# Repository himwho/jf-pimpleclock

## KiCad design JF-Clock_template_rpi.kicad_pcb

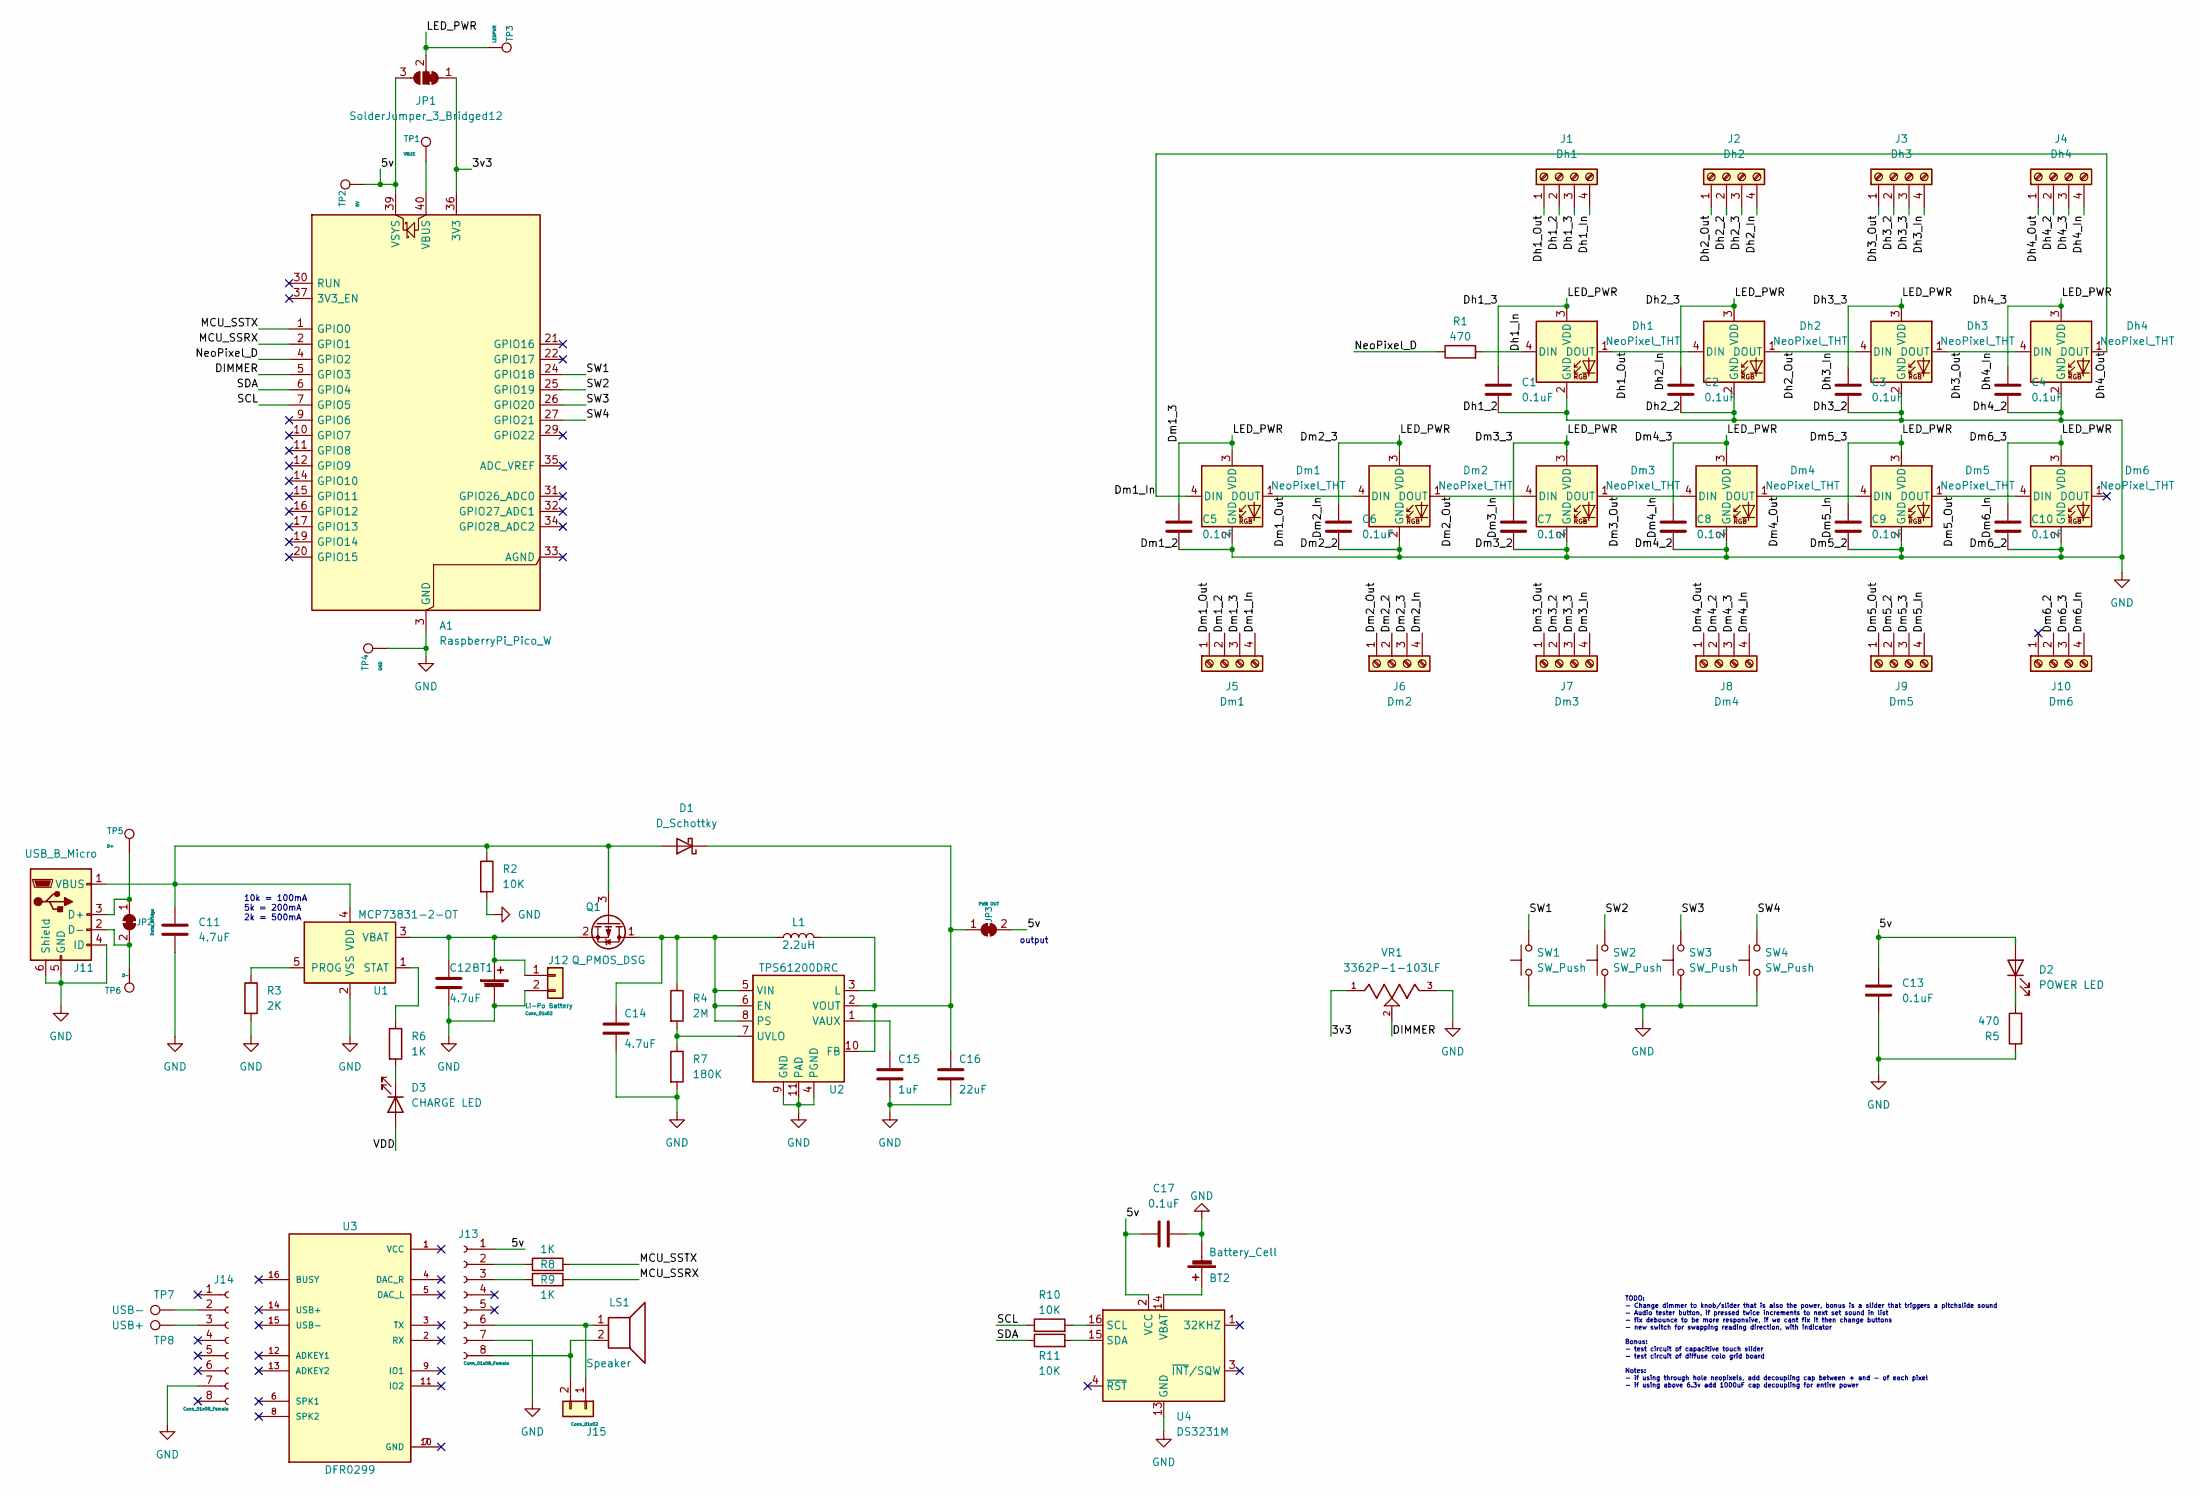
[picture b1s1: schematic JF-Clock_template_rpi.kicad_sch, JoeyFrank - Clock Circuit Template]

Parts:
A1: RaspberryPi_Pico_W; RaspberryPi_Pico_Common_THT
BT1: Li-Po Battery
BT2: Battery_Cell; BatteryHolder_Keystone_1060_1x2032
C1, C2, C3, C4, C5, C6, C7, C8, C9, C10, C13, C17: 0.1uF; C_0805_2012Metric
C11, C12, C14: 4.7uF; C_0805_2012Metric
C15: 1uF; C_0805_2012Metric
C16: 22uF; C_0805_2012Metric
D1: D_Schottky; D_SMA
D2: POWER LED; LED_0603_1608Metric
D3: CHARGE LED; LED_0603_1608Metric
Dh1, Dh2, Dh3, Dh4: NeoPixel_THT; LED_D5.0mm-4_RGB
Dm1, Dm2, Dm3, Dm4, Dm5, Dm6: NeoPixel_THT; LED_D5.0mm-4_RGB
J1: Dh1; TerminalBlock_4Ucon_1x04_P3.50mm_Vertical
J2: Dh2; TerminalBlock_4Ucon_1x04_P3.50mm_Vertical
J3: Dh3; TerminalBlock_4Ucon_1x04_P3.50mm_Vertical
J4: Dh4; TerminalBlock_4Ucon_1x04_P3.50mm_Vertical
J5: Dm1; TerminalBlock_4Ucon_1x04_P3.50mm_Vertical
J6: Dm2; TerminalBlock_4Ucon_1x04_P3.50mm_Vertical
J7: Dm3; TerminalBlock_4Ucon_1x04_P3.50mm_Vertical
J8: Dm4; TerminalBlock_4Ucon_1x04_P3.50mm_Vertical
J9: Dm5; TerminalBlock_4Ucon_1x04_P3.50mm_Vertical
J10: Dm6; TerminalBlock_4Ucon_1x04_P3.50mm_Vertical
J11: USB_B_Micro; USB_Micro-B_Molex-105017-0001
J12: Conn_01x02; JST_PH_S2B-PH-K_1x02_P2.00mm_Horizontal
J13, J14: Conn_01x08_Female; PinHeader_1x08_P2.54mm_Vertical
J15: Conn_01x02; TestPoint_2Pads_Pitch2.54mm_Drill0.8mm
JP1: SolderJumper_3_Bridged12; SolderJumper-3_P1.3mm_Bridged12_RoundedPad1.0x1.5mm_NumberL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
JP2: Data_Bridge; SolderJumper-2_P1.3mm_Bridged_Pad1.0x1.5mm
JP3: PWR OUT; SolderJumper-2_P1.3mm_Bridged_Pad1.0x1.5mm
L1: 2.2uH; L_0603_1608Metric
LS1: Speaker; TestPoint_Bridge_Pitch2.54mm_Drill1.0mm
Q1: Q_PMOS_DSG; SOT-23
R1, R5: 470; R_0805_2012Metric
R2, R10, R11: 10K; R_0805_2012Metric
R3: 2K; R_0805_2012Metric
R4: 2M; R_0805_2012Metric
R6, R8, R9: 1K; R_0805_2012Metric
R7: 180K; R_0805_2012Metric
SW1, SW2, SW3, SW4: SW_Push; SW_PUSH_6mm_H5mm
TP1: VBUS; TestPoint_THTPad_2.5x2.5mm_Drill1.2mm
TP2: 5V; TestPoint_THTPad_2.5x2.5mm_Drill1.2mm
TP3: LEDPWR; TestPoint_THTPad_2.5x2.5mm_Drill1.2mm
TP4: GND; TestPoint_THTPad_2.5x2.5mm_Drill1.2mm
TP5: D+; TestPoint_THTPad_2.5x2.5mm_Drill1.2mm
TP6: D-; TestPoint_THTPad_2.5x2.5mm_Drill1.2mm
TP7: USB-; TestPoint_THTPad_2.5x2.5mm_Drill1.2mm
TP8: USB+; TestPoint_THTPad_2.5x2.5mm_Drill1.2mm
U1: MCP73831-2-OT; SOT-23-5
U2: TPS61200DRC; Texas_S-PVSON-N10_ThermalVias
U3: DFR0299; DFPlayer_V2
U4: DS3231M; SOIC-16W_7.5x10.3mm_P1.27mm
VR1: 3362P-1-103LF; TRIM_3362P-1-103LF

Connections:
/3v3: A1.36 (3V3), JP1.1 (A), VR1.1
/5v: A1.39 (VSYS), C13.1, C17.2, D2.2 (A), J13.1, JP1.3 (B), JP3.2 (B), TP2.1, U4.2 (VCC)
/DIMMER: A1.5 (GPIO3), VR1.2
/Dh1_3: C1.1, C2.1, C3.1, C4.1, C5.1, C6.1, C7.1, C8.1, C9.1, C10.1, Dh1.3 (VDD), Dh2.3 (VDD), Dh3.3 (VDD), Dh4.3 (VDD), Dm1.3 (VDD), Dm2.3 (VDD), Dm3.3 (VDD), Dm4.3 (VDD), Dm5.3 (VDD), Dm6.3 (VDD), J1.3, J2.3, J3.3, J4.3, J5.3, J6.3, J7.3, J8.3, J9.3, J10.3, JP1.2 (C), TP3.1
/Dh1_In: Dh1.4 (DIN), J1.4, R1.2
/Dh1_Out: Dh1.1 (DOUT), Dh2.4 (DIN), J1.1, J2.4
/Dh2_Out: Dh2.1 (DOUT), Dh3.4 (DIN), J2.1, J3.4
/Dh3_Out: Dh3.1 (DOUT), Dh4.4 (DIN), J3.1, J4.4
/Dh4_Out: Dh4.1 (DOUT), Dm1.4 (DIN), J4.1, J5.4
/Dm1_Out: Dm1.1 (DOUT), Dm2.4 (DIN), J5.1, J6.4
/Dm2_Out: Dm2.1 (DOUT), Dm3.4 (DIN), J6.1, J7.4
/Dm3_Out: Dm3.1 (DOUT), Dm4.4 (DIN), J7.1, J8.4
/Dm4_Out: Dm4.1 (DOUT), Dm5.4 (DIN), J8.1, J9.4
/Dm5_Out: Dm5.1 (DOUT), Dm6.4 (DIN), J9.1, J10.4
/MCU_SSRX: A1.2 (GPIO1), R9.2
/MCU_SSTX: A1.1 (GPIO0), R8.2
/NeoPixel_D: A1.4 (GPIO2), R1.1
/SCL: A1.7 (GPIO5), R10.1
/SDA: A1.6 (GPIO4), R11.1
/SW1: A1.24 (GPIO18), SW1.2
/SW2: A1.25 (GPIO19), SW2.2
/SW3: A1.26 (GPIO20), SW3.2
/SW4: A1.27 (GPIO21), SW4.2
/VDD: D3.2 (A)
GND: A1.3 (GND), A1.8 (GND), A1.13 (GND), A1.18 (GND), A1.23 (GND), A1.28 (GND), A1.38 (GND), BT1.2 (-), BT2.2 (-), C1.2, C2.2, C3.2, C4.2, C5.2, C6.2, C7.2, C8.2, C9.2, C10.2, C11.2, C12.2, C13.2, C14.2, C15.2, C16.2, C17.1, Dh1.2 (GND), Dh2.2 (GND), Dh3.2 (GND), Dh4.2 (GND), Dm1.2 (GND), Dm2.2 (GND), Dm3.2 (GND), Dm4.2 (GND), Dm5.2 (GND), Dm6.2 (GND), J1.2, J2.2, J3.2, J4.2, J5.2, J6.2, J7.2, J8.2, J9.2, J10.2, J11.4 (ID), J11.5 (GND), J11.6 (Shield), J12.2, J13.7, J14.7, R2.2, R3.2, R5.1, R7.2, SW1.1, SW2.1, SW3.1, SW4.1, TP4.1, U1.2 (VSS), U2.4 (PGND), U2.9 (GND), U2.11 (PAD), U4.5 (GND), U4.6 (GND), U4.7 (GND), U4.8 (GND), U4.9 (GND), U4.10 (GND), U4.11 (GND), U4.12 (GND), U4.13 (GND), VR1.3
unnamed: A1.40 (VBUS), TP1.1
unnamed: BT2.1 (+), U4.14 (VBAT)
unnamed: C11.1, D1.2 (A), J11.1 (VBUS), Q1.3 (G), R2.1, U1.4 (VDD)
unnamed: C16.1, D1.1 (K), JP3.1 (A), U2.2 (VOUT), U2.10 (FB)
unnamed: D2.1 (K), R5.2
unnamed: D3.1 (K), R6.2
unnamed: J11.3 (D+), JP2.1 (A), TP5.1
unnamed: J11.2 (D-), JP2.2 (B), TP6.1
unnamed: BT1.1 (+), C12.1, J12.1, Q1.2 (S), U1.3 (VBAT)
unnamed: J13.2, R8.1
unnamed: J13.3, R9.1
unnamed: J13.6, J15.1, LS1.1
unnamed: J13.8, J15.2, LS1.2
unnamed: J14.2, TP7.1
unnamed: J14.3, TP8.1
unnamed: C14.1, L1.1, Q1.1 (D), R4.1, U2.5 (VIN), U2.6 (EN), U2.8 (PS)
unnamed: R3.1, U1.5 (PROG)
unnamed: R6.1, U1.1 (STAT)
unnamed: L1.2, U2.3 (L)
unnamed: R4.2, R7.1, U2.7 (UVLO)
unnamed: C15.1, U2.1 (VAUX)
unnamed: U3.7 (GND), U3.10 (GND)
unnamed: R10.2, U4.16 (SCL)
unnamed: R11.2, U4.15 (SDA)

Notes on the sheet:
10k = 100mA 5k = 200mA 2k = 500mA
TODO: - Change dimmer to knob/slider that is also the power, bonus is a slider that triggers a pitchslide sound - Audio tester button, if pressed twice increments to next set sound in list - fix debounce to be more responsive, if we cant fix it then change buttons - new switch for swapping reading 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
output

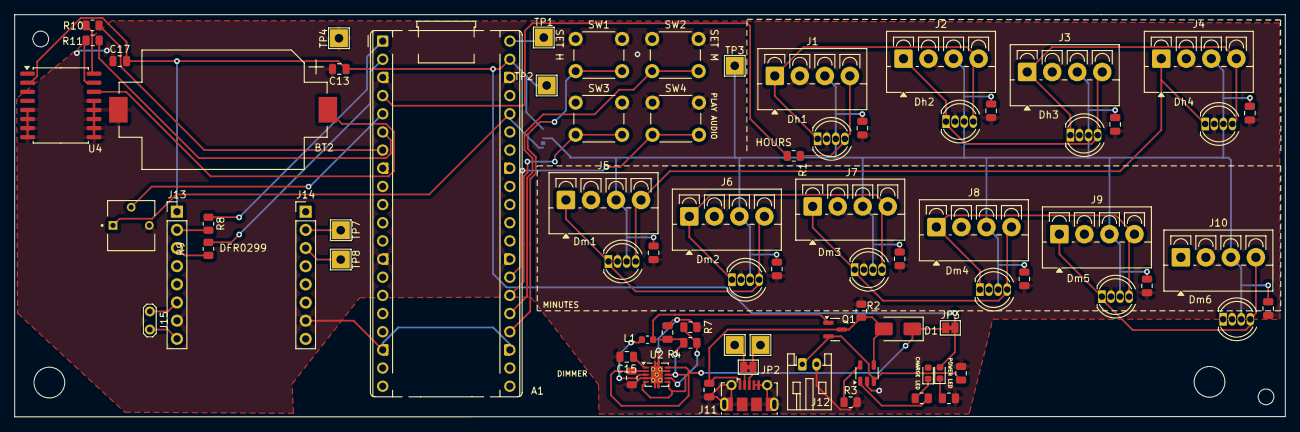
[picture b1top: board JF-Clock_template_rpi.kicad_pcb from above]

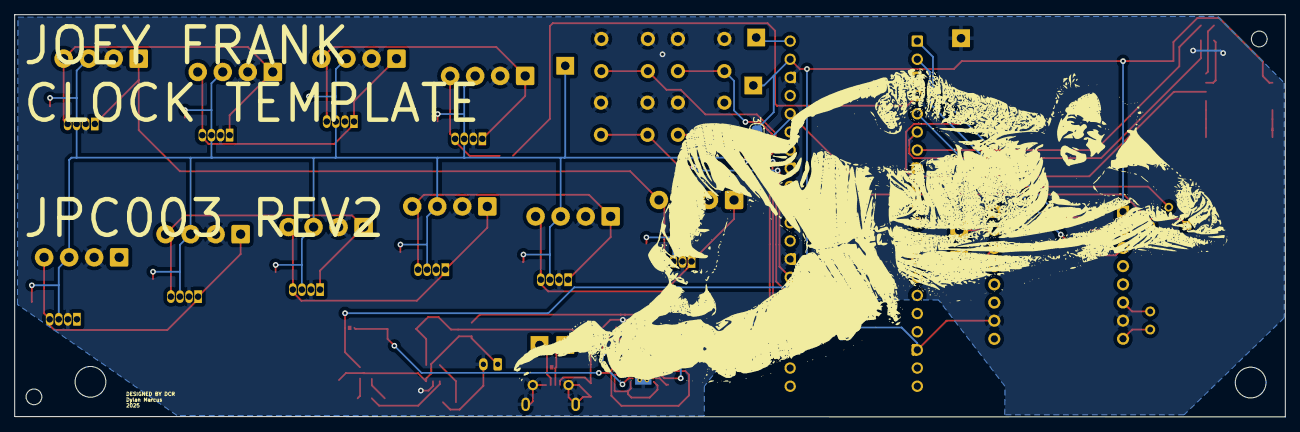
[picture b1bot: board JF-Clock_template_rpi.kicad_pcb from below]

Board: 2 copper layers, 177.7 x 56.2 mm, 84 parts (2 on the bottom side), 47 nets.

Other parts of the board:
DrillHole1, DrillHole2: MountingHole_2.2mm_M2
DrillHole3, DrillHole4: MountingHole_4.3mm_M4
JF: 1; ec2f3285-075e-41d4-8f47-5025fa669693

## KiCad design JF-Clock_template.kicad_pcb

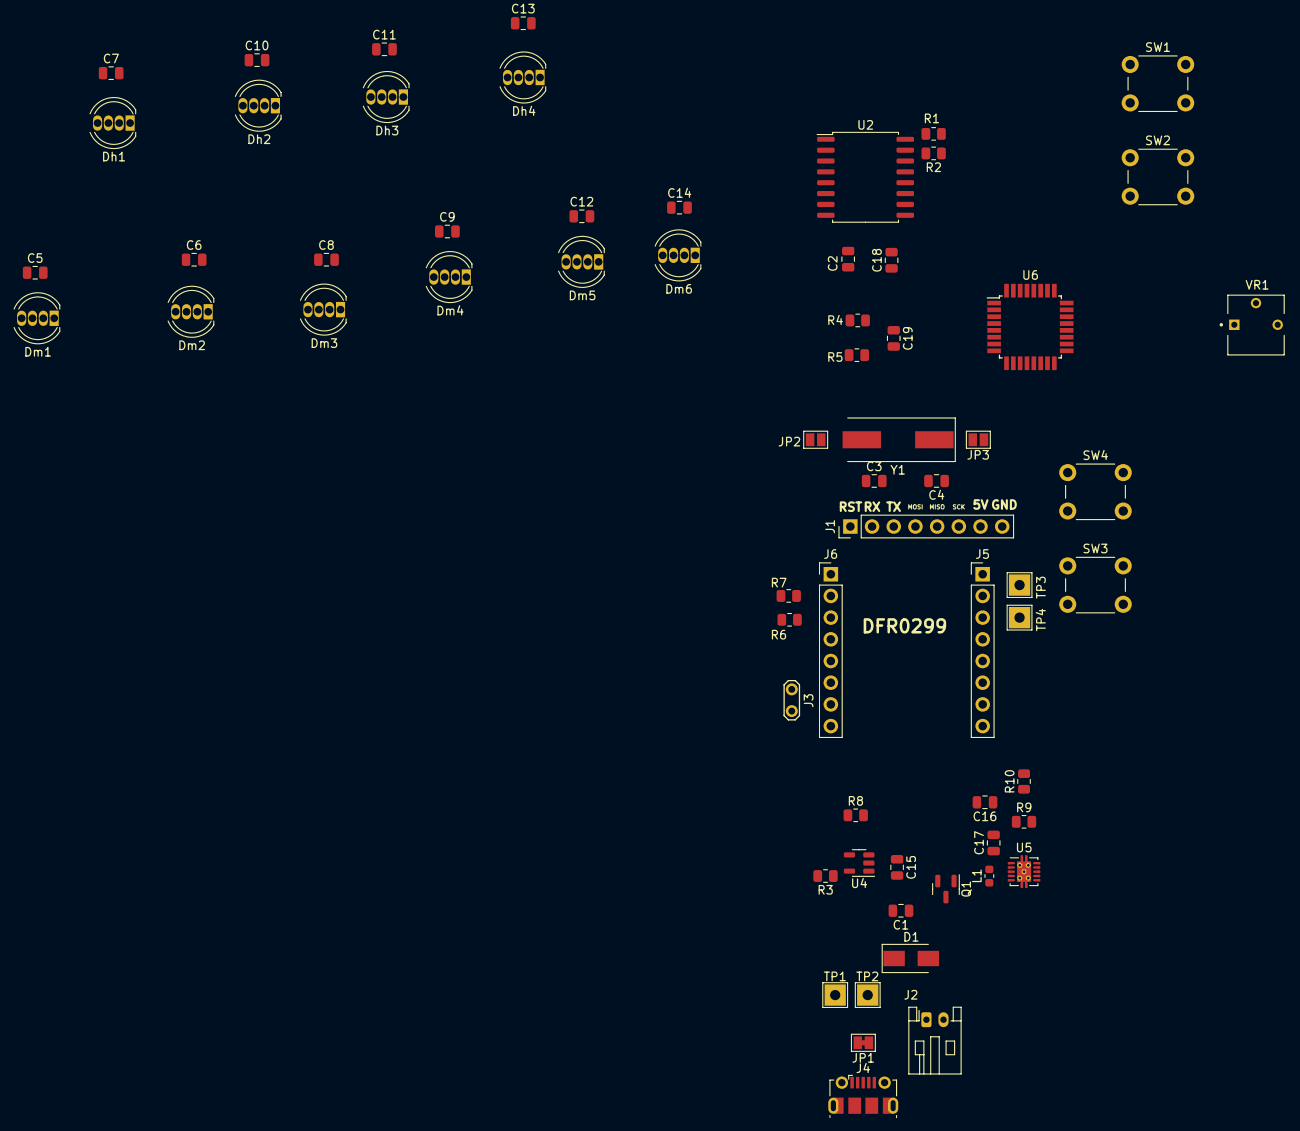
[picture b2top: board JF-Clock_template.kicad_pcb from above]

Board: 2 copper layers, 66 parts (1 on the bottom side), 50 nets, no tracks yet.

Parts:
BT1: Battery_Cell; BatteryHolder_Keystone_1060_1x2032
C1, C15, C16: 4.7uF; C_0805_2012Metric
C2, C5, C6, C7, C8, C9, C10, C11, C12, C13, C14: 0.1uF; C_0805_2012Metric
C3, C4: 22pF; C_0805_2012Metric
C17: 1uF; C_0805_2012Metric
C18: 22uF; C_0805_2012Metric
C19: 100nF; C_0805_2012Metric
D1: D_Schottky; D_SMA
Dh1, Dh2, Dh3, Dh4: NeoPixel_THT; LED_D5.0mm-4_RGB
Dm1, Dm2, Dm3, Dm4, Dm5, Dm6: NeoPixel_THT; LED_D5.0mm-4_RGB
J1, J5, J6: Conn_01x08_Female; PinHeader_1x08_P2.54mm_Vertical
J2: Conn_01x02; JST_PH_S2B-PH-K_1x02_P2.00mm_Horizontal
J3: Conn_01x02; TestPoint_2Pads_Pitch2.54mm_Drill0.8mm
J4: USB_B_Micro; USB_Micro-B_Molex-105017-0001
JP1: Data_Bridge; SolderJumper-2_P1.3mm_Bridged_Pad1.0x1.5mm
JP2: XTAL_1; SolderJumper-2_P1.3mm_Open_Pad1.0x1.5mm
JP3: XTAL_2; SolderJumper-2_P1.3mm_Open_Pad1.0x1.5mm
L1: 2.2uH; L_0603_1608Metric
Q1: Q_PMOS_DSG; SOT-23
R1, R2, R4, R8: 10K; R_0805_2012Metric
R3: 2K; R_0805_2012Metric
R5: 470; R_0805_2012Metric
R6, R7: 1K; R_0805_2012Metric
R9: 2M; R_0805_2012Metric
R10: 180K; R_0805_2012Metric
SW1, SW2, SW3, SW4: SW_Push; SW_PUSH_6mm_H5mm
TP1: D+; TestPoint_THTPad_2.5x2.5mm_Drill1.2mm
TP2: D-; TestPoint_THTPad_2.5x2.5mm_Drill1.2mm
TP3: USB-; TestPoint_THTPad_2.5x2.5mm_Drill1.2mm
TP4: USB+; TestPoint_THTPad_2.5x2.5mm_Drill1.2mm
U2: DS3231M; SOIC-16W_7.5x10.3mm_P1.27mm
U4: MCP73831-2-OT; SOT-23-5
U5: TPS61200DRC; Texas_S-PVSON-N10_ThermalVias
U6: ATmega328P-A; TQFP-32_7x7mm_P0.8mm
VR1: 3362P-1-103LF; TRIM_3362P-1-103LF
Y1: 16Mhz; Crystal_SMD_HC49-SD

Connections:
/5v: C2.1, C5.1, C6.1, C7.1, C8.1, C9.1, C10.1, C11.1, C12.1, C13.1, C14.1, C18.1, C19.2, D1.1 (K), Dh1.3 (VDD), Dh2.3 (VDD), Dh3.3 (VDD), Dh4.3 (VDD), Dm1.3 (VDD), Dm2.3 (VDD), Dm3.3 (VDD), Dm4.3 (VDD), Dm5.3 (VDD), Dm6.3 (VDD), J1.7, J6.1, R4.2, U2.2 (VCC), U5.2 (VOUT), U5.10 (FB), U6.4 (VCC), U6.6 (VCC), U6.18 (AVCC), VR1.1
/DIMMER: U6.26 (PC3), VR1.2
/MCU_RX: J1.2, U6.30 (PD0)
/MCU_SSRX: R6.2, U6.9 (PD5)
/MCU_SSTX: R7.2, U6.10 (PD6)
/MCU_TX: J1.3, U6.31 (PD1)
/MISO: J1.5, U6.16 (PB4)
/MOSI: J1.4, U6.15 (PB3)
/NeoPixel_D: R5.1, U6.2 (PD4)
/RESET: J1.1, R4.1, U6.29 (~RESET/PC6)
/SCK: J1.6, U6.17 (PB5)
/SCL: R1.1, U6.28 (PC5)
/SDA: R2.1, U6.27 (PC4)
/SW1: SW1.2, U6.32 (PD2)
/SW2: SW2.2, U6.1 (PD3)
/SW3: SW3.2, U6.12 (PB0)
/SW4: SW4.2, U6.13 (PB1)
GND: BT1.2 (-), C1.2, C2.2, C3.2, C4.2, C5.2, C6.2, C7.2, C8.2, C9.2, C10.2, C11.2, C12.2, C13.2, C14.2, C15.2, C16.2, C17.2, C18.2, C19.1, Dh1.2 (GND), Dh2.2 (GND), Dh3.2 (GND), Dh4.2 (GND), Dm1.2 (GND), Dm2.2 (GND), Dm3.2 (GND), Dm4.2 (GND), Dm5.2 (GND), Dm6.2 (GND), J1.8, J2.2, J4.4 (ID), J4.5 (GND), J4.6 (Shield), J5.7, J6.7, R3.2, R8.2, R10.2, SW1.1, SW2.1, SW3.1, SW4.1, U2.5 (GND), U2.6 (GND), U2.7 (GND), U2.8 (GND), U2.9 (GND), U2.10 (GND), U2.11 (GND), U2.12 (GND), U2.13 (GND), U4.2 (VSS), U5.4 (PGND), U5.9 (GND), U5.11 (PAD), U6.3 (GND), U6.5 (GND), U6.21 (GND), VR1.3
unnamed: BT1.1 (+), U2.14 (VBAT)
unnamed: C15.1, J2.1, Q1.2 (S), U4.3 (VBAT)
unnamed: C1.1, D1.2 (A), J4.1 (VBUS), Q1.3 (G), R8.1, U4.4 (VDD)
unnamed: C3.1, JP2.2 (B), Y1.2
unnamed: C4.1, JP3.2 (B), Y1.1
unnamed: C16.1, L1.1, Q1.1 (D), R9.1, U5.5 (VIN), U5.6 (EN), U5.8 (PS)
unnamed: C17.1, U5.1 (VAUX)
unnamed: Dh1.1 (DOUT), Dh2.4 (DIN)
unnamed: Dh1.4 (DIN), R5.2
unnamed: Dh2.1 (DOUT), Dh3.4 (DIN)
unnamed: Dh3.1 (DOUT), Dh4.4 (DIN)
unnamed: Dh4.1 (DOUT), Dm1.4 (DIN)
unnamed: Dm1.1 (DOUT), Dm2.4 (DIN)
unnamed: Dm2.1 (DOUT), Dm3.4 (DIN)
unnamed: Dm3.1 (DOUT), Dm4.4 (DIN)
unnamed: Dm4.1 (DOUT), Dm5.4 (DIN)
unnamed: Dm5.1 (DOUT), Dm6.4 (DIN)
unnamed: J3.1, J6.6
unnamed: J3.2, J6.8
unnamed: J4.2 (D-), JP1.2 (B), TP2.1
unnamed: J4.3 (D+), JP1.1 (A), TP1.1
unnamed: J5.2, TP3.1
unnamed: J5.3, TP4.1
unnamed: J6.2, R7.1
unnamed: J6.3, R6.1
unnamed: JP2.1 (A), U6.7 (XTAL1/PB6)
unnamed: JP3.1 (A), U6.8 (XTAL2/PB7)
unnamed: L1.2, U5.3 (L)
unnamed: R1.2, U2.16 (SCL)
unnamed: R2.2, U2.15 (SDA)
unnamed: R3.1, U4.5 (PROG)
unnamed: R9.2, R10.1, U5.7 (UVLO)

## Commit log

2023-01-05 initial commit of revision 1 schem
2023-01-07 init for new voltage regulator and lipo management
2023-01-11 init for pcb layout with test outline silk and shape
2023-01-13 started first pcb test layout and some part assignment to jcl
2023-01-13 update pcb layout, swapped a few parts to make them easier for assembly
2023-01-14 revisions for pcb layout, new cheaper parts selected, this went out into a test production
2023-01-30 init for experimental next version ino
2023-02-01 small circuit tweak for fixing missing vcc/avcc ref for bootloader
2023-03-17 revision 2, changed some parts for making it easier to manufacture, fixed the issue with the wrong atmega footprint, added more test points
2023-05-07 init for dfplayer lib
2023-05-07 fixed 1pm bug, fixed position of M and H buttons
2023-05-07 working audio player
2023-05-07 fixed hour and minute led display based on new circuit
2023-05-07 fix color and added dimmer
2025-06-18 init for python version on pico W
2025-06-18 update from projects
2025-08-01 update for project
